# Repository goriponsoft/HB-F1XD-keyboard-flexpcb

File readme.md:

# HB-F1X series keyboard sheet replacement PCB (Flex PCB version)
Based on the data created by S0urceror, we created a Flex PCB version to replace the keyboard sheet.

Operation has been confirmed on the actual HB-F1XD and HB-F1XV. :-)

## Creative Commons - BY NC - license
This data inherits the license of the original data.

Regarding use outside the scope of the license, GORIPON and GORIPON HARDWARE are not concerned and will follow the original author's judgment.

Please contact the original author sourceror_at_neximus_dot_com for any inquiries.

## Files
The PCB and schematics are made for KiCAD.

In KiCAD you can generate the Gerber files and send them to your PCB manufacturer.

## Components
* 1x PCB
* 1x 0.1mm thick plastic board
* 1x double-sided tape

(Since it is difficult to insert the connector as is, it is necessary to attach a thin plastic plate to the connector contact area.)

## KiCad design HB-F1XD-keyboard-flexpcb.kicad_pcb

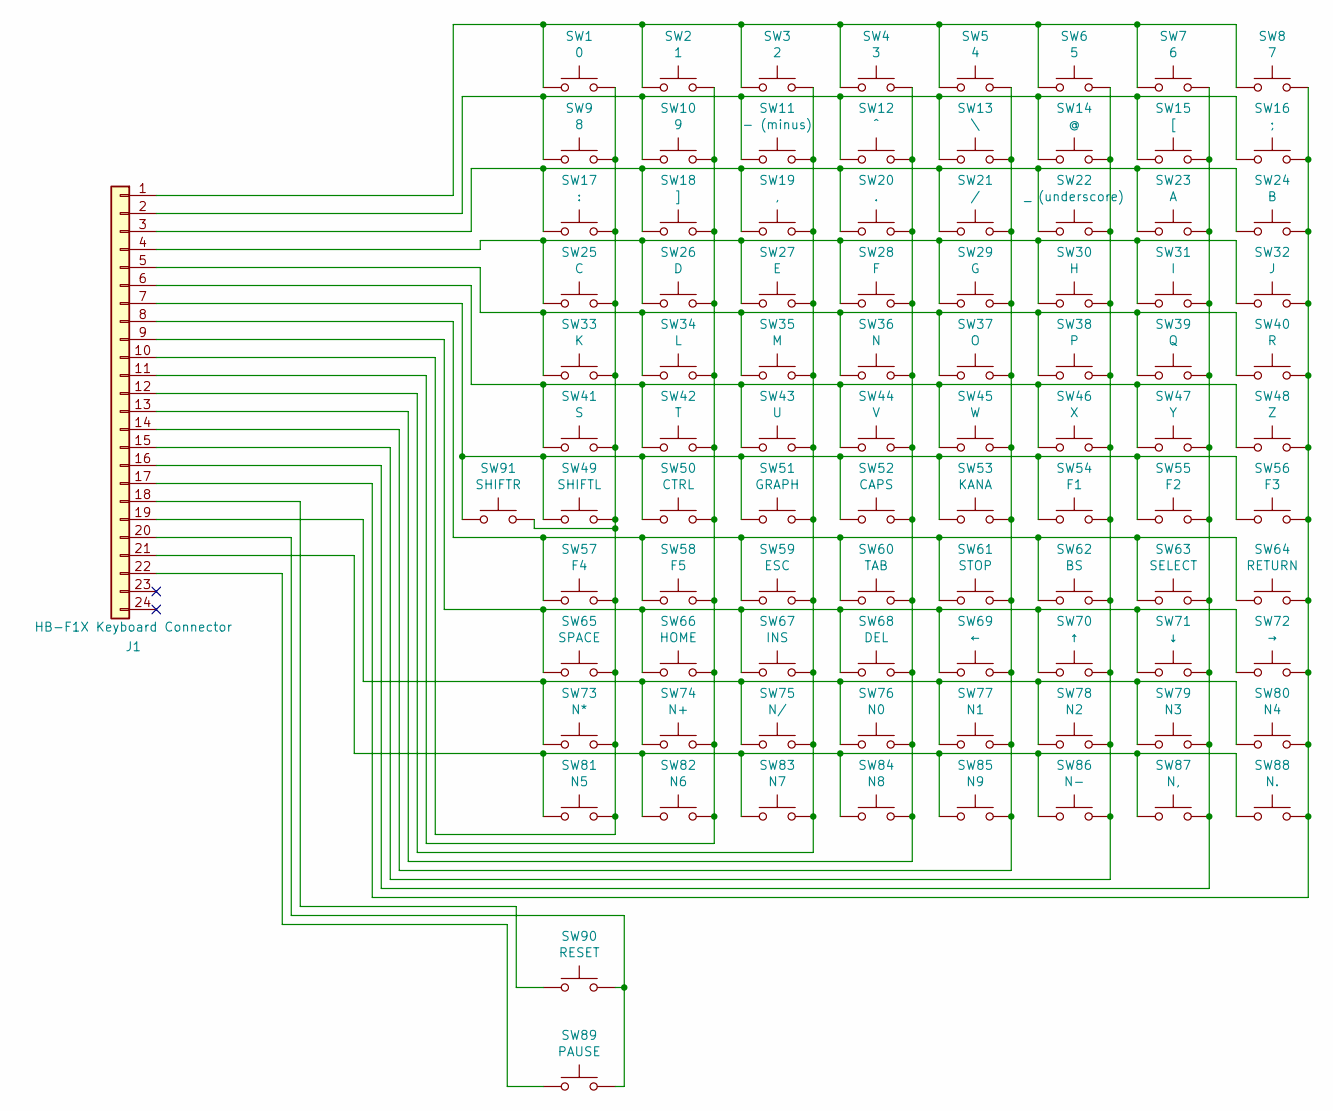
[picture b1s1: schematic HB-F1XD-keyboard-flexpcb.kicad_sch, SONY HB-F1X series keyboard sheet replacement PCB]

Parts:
J1: HB-F1X Keyboard Connector; edge_connector
SW1: 0; key-diagonal-beauty
SW2: 1; key-diagonal-beauty
SW3: 2; key-diagonal-beauty
SW4: 3; key-diagonal-beauty
SW5: 4; key-diagonal-beauty
SW6: 5; key-diagonal-beauty
SW7: 6; key-diagonal-beauty
SW8: 7; key-diagonal-beauty
SW9: 8; key-diagonal-beauty
SW10: 9; key-diagonal-beauty
SW11: - (minus); key-diagonal-beauty
SW12: ^; key-diagonal-beauty
SW13: \; key-diagonal-beauty
SW14: @; key-diagonal-beauty
SW15: [; key-diagonal-beauty
SW16: ;; key-diagonal-beauty
SW17: :; key-diagonal-beauty
SW18: ]; key-diagonal-beauty
SW19: ,; key-diagonal-beauty
SW20: .; key-diagonal-beauty
SW21: /; key-diagonal-beauty
SW22: _ (underscore); key-diagonal-beauty
SW23: A; key-diagonal-beauty
SW24: B; key-diagonal-beauty
SW25: C; key-diagonal-beauty
SW26: D; key-diagonal-beauty
SW27: E; key-diagonal-beauty
SW28: F; key-diagonal-beauty
SW29: G; key-diagonal-beauty
SW30: H; key-diagonal-beauty
SW31: I; key-diagonal-beauty
SW32: J; key-diagonal-beauty
SW33: K; key-diagonal-beauty
SW34: L; key-diagonal-beauty
SW35: M; key-diagonal-beauty
SW36: N; key-diagonal-beauty
SW37: O; key-diagonal-beauty
SW38: P; key-diagonal-beauty
SW39: Q; key-diagonal-beauty
SW40: R; key-diagonal-beauty
SW41: S; key-diagonal-beauty
SW42: T; key-diagonal-beauty
SW43: U; key-diagonal-beauty
SW44: V; key-diagonal-beauty
SW45: W; key-diagonal-beauty
SW46: X; key-diagonal-beauty
SW47: Y; key-diagonal-beauty
SW48: Z; key-diagonal-beauty
SW49: SHIFTL; key-diagonal-beauty
SW50: CTRL; key-diagonal-beauty
SW51: GRAPH; key-diagonal-beauty
SW52: CAPS; key-diagonal-beauty
SW53: KANA; key-diagonal-beauty
SW54: F1; key-horizontal-beauty
SW55: F2; key-horizontal-beauty
SW56: F3; key-horizontal-beauty
SW57: F4; key-horizontal-beauty
SW58: F5; key-horizontal-beauty
SW59: ESC; key-diagonal-beauty
SW60: TAB; key-diagonal-beauty
SW61: STOP; key-horizontal-beauty
SW62: BS; key-diagonal-beauty
SW63: SELECT; key-diagonal-beauty
SW64: RETURN; key-diagonal-beauty
SW65: SPACE; key-diagonal-beauty
SW66: HOME; key-horizontal-beauty
SW67: INS; key-horizontal-beauty
SW68: DEL; key-horizontal-beauty
SW69: ←; key-diagonal-beauty
SW70: ↑; key-diagonal-beauty
SW71: ↓; key-diagonal-beauty
SW72: →; key-diagonal-beauty
SW73: N*; key-diagonal-beauty
SW74: N+; key-diagonal-beauty
SW75: N/; key-diagonal-beauty
SW76: N0; key-diagonal-beauty
SW77: N1; key-diagonal-beauty
SW78: N2; key-diagonal-beauty
SW79: N3; key-diagonal-beauty
SW80: N4; key-diagonal-beauty
SW81: N5; key-diagonal-beauty
SW82: N6; key-diagonal-beauty
SW83: N7; key-diagonal-beauty
SW84: N8; key-diagonal-beauty
SW85: N9; key-diagonal-beauty
SW86: N-; key-diagonal-beauty
SW87: N,; key-diagonal-beauty
SW88: N.; key-diagonal-beauty
SW89: PAUSE; key-horizontal-beauty
SW90: RESET; key-reset
SW91: SHIFTR; key-diagonal-beauty

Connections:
unnamed: J1.1, SW1.1, SW2.1, SW3.1, SW4.1, SW5.1, SW6.1, SW7.1, SW8.1
unnamed: J1.2, SW9.1, SW10.1, SW11.1, SW12.1, SW13.1, SW14.1, SW15.1, SW16.1
unnamed: J1.3, SW17.1, SW18.1, SW19.1, SW20.1, SW21.1, SW22.1, SW23.1, SW24.1
unnamed: J1.4, SW25.1, SW26.1, SW27.1, SW28.1, SW29.1, SW30.1, SW31.1, SW32.1
unnamed: J1.5, SW33.1, SW34.1, SW35.1, SW36.1, SW37.1, SW38.1, SW39.1, SW40.1
unnamed: J1.6, SW41.1, SW42.1, SW43.1, SW44.1, SW45.1, SW46.1, SW47.1, SW48.1
unnamed: J1.7, SW49.1, SW50.1, SW51.1, SW52.1, SW53.1, SW54.1, SW55.1, SW56.1, SW91.1
unnamed: J1.8, SW57.1, SW58.1, SW59.1, SW60.1, SW61.1, SW62.1, SW63.1, SW64.1
unnamed: J1.9, SW65.1, SW66.1, SW67.1, SW68.1, SW69.1, SW70.1, SW71.1, SW72.1
unnamed: J1.10, SW1.2, SW9.2, SW17.2, SW25.2, SW33.2, SW41.2, SW49.2, SW57.2, SW65.2, SW73.2, SW81.2, SW91.2
unnamed: J1.11, SW2.2, SW10.2, SW18.2, SW26.2, SW34.2, SW42.2, SW50.2, SW58.2, SW66.2, SW74.2, SW82.2
unnamed: J1.12, SW3.2, SW11.2, SW19.2, SW27.2, SW35.2, SW43.2, SW51.2, SW59.2, SW67.2, SW75.2, SW83.2
unnamed: J1.13, SW4.2, SW12.2, SW20.2, SW28.2, SW36.2, SW44.2, SW52.2, SW60.2, SW68.2, SW76.2, SW84.2
unnamed: J1.14, SW5.2, SW13.2, SW21.2, SW29.2, SW37.2, SW45.2, SW53.2, SW61.2, SW69.2, SW77.2, SW85.2
unnamed: J1.15, SW6.2, SW14.2, SW22.2, SW30.2, SW38.2, SW46.2, SW54.2, SW62.2, SW70.2, SW78.2, SW86.2
unnamed: J1.16, SW7.2, SW15.2, SW23.2, SW31.2, SW39.2, SW47.2, SW55.2, SW63.2, SW71.2, SW79.2, SW87.2
unnamed: J1.17, SW8.2, SW16.2, SW24.2, SW32.2, SW40.2, SW48.2, SW56.2, SW64.2, SW72.2, SW80.2, SW88.2
unnamed: J1.18, SW90.1
unnamed: J1.19, SW73.1, SW74.1, SW75.1, SW76.1, SW77.1, SW78.1, SW79.1, SW80.1
unnamed: J1.20, SW89.2, SW90.2
unnamed: J1.21, SW81.1, SW82.1, SW83.1, SW84.1, SW85.1, SW86.1, SW87.1, SW88.1
unnamed: J1.22, SW89.1

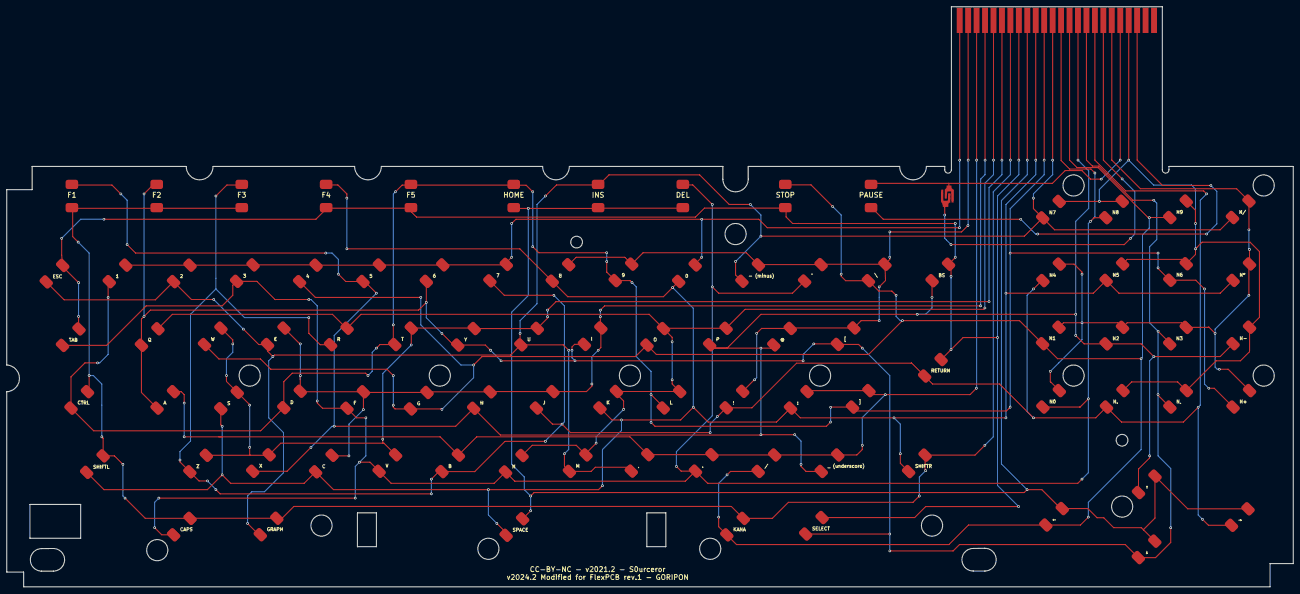
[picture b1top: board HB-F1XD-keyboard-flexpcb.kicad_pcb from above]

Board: 2 copper layers, 386.7 x 174.4 mm, 92 parts (0 on the bottom side), 22 nets.

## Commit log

2024-02-01 First release
    First release
2024-02-01 Original author name corrected.
    Original author name corrected.
2024-02-01 Fixed line breaks in readme.md.
    Fixed line breaks in readme.md.

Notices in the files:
HB-F1XD-keyboard-flexpcb.kicad_pcb:
CC-BY-NC - v2021.2 - S0urceror
